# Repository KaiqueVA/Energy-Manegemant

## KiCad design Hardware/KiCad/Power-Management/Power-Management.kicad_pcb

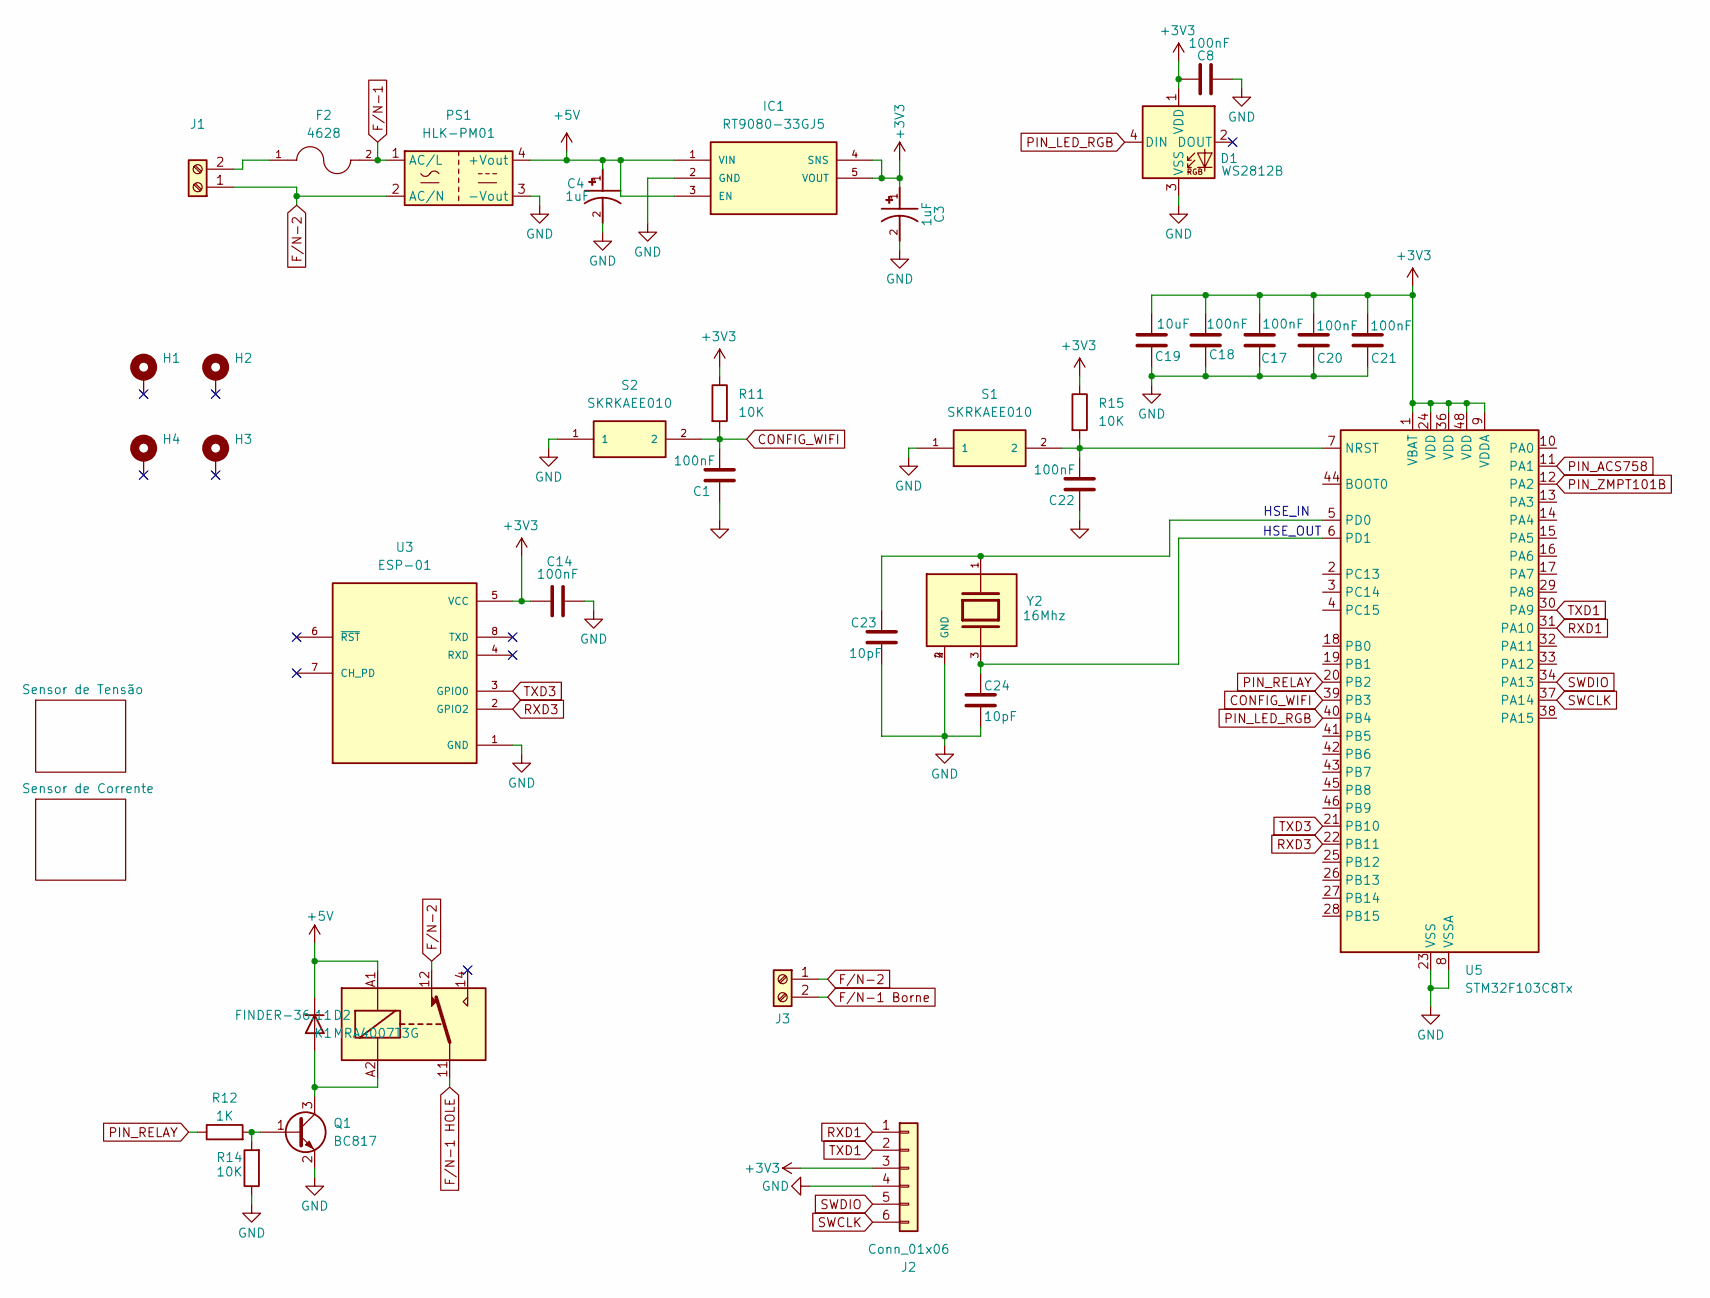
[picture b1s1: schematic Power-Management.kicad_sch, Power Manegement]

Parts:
C1, C8, C14, C17, C18, C20, C21, C22: 100nF; C_0805_2012Metric
C3, C4: 1uF; CAPMP3216X180N; PARTREV N/A
C19: 10uF; C_0805_2012Metric
C23, C24: 10pF; C_0805_2012Metric
D1: WS2812B; LED_WS2812B_PLCC4_5.0x5.0mm_P3.2mm
D2: MRA4007T3G; D_SMA_Handsoldering
F2: 4628; FUSE_4628
H1, H2, H3, H4: MountingHole_Pad; MountingHole_3.2mm_M3_Pad_Via
IC1: RT9080-33GJ5; SOT94P280X100-5N; Mouser_Part_Number 835-RT9080-33GJ5
J1, J3: Screw_Terminal_01x02; TerminalBlock_Altech_AK300-2_P5.00mm
J2: Conn_01x06; Molex_KK-254_AE-6410-06A_1x06_P2.54mm_Vertical
K1: FINDER-36.11; Relay_SPDT_Finder_36.11
PS1: HLK-PM01; Converter_ACDC_Hi-Link_HLK-PMxx
Q1: BC817; SOT-23
R11, R14, R15: 10K; R_0805_2012Metric_Pad1.20x1.40mm_HandSolder
R12: 1K; R_0805_2012Metric_Pad1.20x1.40mm_HandSolder
S1, S2: SKRKAEE010; SKRK; Manufacturer_Part_Number SKRKAEE010
U3: ESP-01; MODULE_ESP-01; PARTREV 1.0
U5: STM32F103C8Tx; LQFP-48_7x7mm_P0.5mm
Y2: 16Mhz; XTAL_TSX-3225_25.0000MF10Z-W; PARTREV N/A

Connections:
+3V3: C3.1, C8.2, C14.1, C17.2, C18.2, C19.2, C20.2, C21.2, D1.1 (VDD), IC1.4 (SNS), IC1.5 (VOUT), J2.3, R11.1, R15.1, U3.5 (VCC), U5.1 (VBAT), U5.9 (VDDA), U5.24 (VDD), U5.36 (VDD), U5.48 (VDD); also elsewhere on the board
+5V: C4.1, D2.1 (K), IC1.1 (VIN), IC1.3 (EN), K1.A1, PS1.4 (+Vout); also elsewhere on the board
CONFIG_WIFI: C1.2, R11.2, S2.2, U5.39 (PB3)
F/N-1: F2.2, PS1.1 (AC/L); also elsewhere on the board
F/N-1 Borne: J3.2; also elsewhere on the board
F/N-1 HOLE: K1.11; also elsewhere on the board
F/N-2: J1.1, J3.1, K1.12, PS1.2 (AC/N); also elsewhere on the board
GND: C1.1, C3.2, C4.2, C8.1, C14.2, C17.1, C18.1, C19.1, C20.1, C21.1, C22.1, C23.1, C24.1, D1.3 (VSS), IC1.2 (GND), J2.4, PS1.3 (-Vout), Q1.2 (E), R14.1, S1.1, S2.1, U3.1 (GND), U5.8 (VSSA), U5.23 (VSS), U5.35 (VSS), U5.47 (VSS), Y2.2 (GND), Y2.4 (GND); also elsewhere on the board
unnamed: D2.2 (A), K1.A2, Q1.3 (C)
unnamed: F2.1, J1.2
unnamed: Q1.1 (B), R12.2, R14.2
unnamed: C22.2, R15.2, S1.2, U5.7 (NRST)
unnamed: C23.2, U5.5 (PD0), Y2.1
unnamed: C24.2, U5.6 (PD1), Y2.3
PIN_ACS758: U5.11 (PA1); also elsewhere on the board
PIN_LED_RGB: D1.4 (DIN), U5.40 (PB4)
PIN_RELAY: R12.1, U5.20 (PB2)
PIN_ZMPT101B: U5.12 (PA2); also elsewhere on the board
RXD1: J2.1, U5.31 (PA10)
RXD3: U3.2 (GPIO2), U5.22 (PB11)
SWCLK: J2.6, U5.37 (PA14)
SWDIO: J2.5, U5.34 (PA13)
TXD1: J2.2, U5.30 (PA9)
TXD3: U3.3 (GPIO0), U5.21 (PB10)

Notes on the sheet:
HSE_IN
HSE_OUT

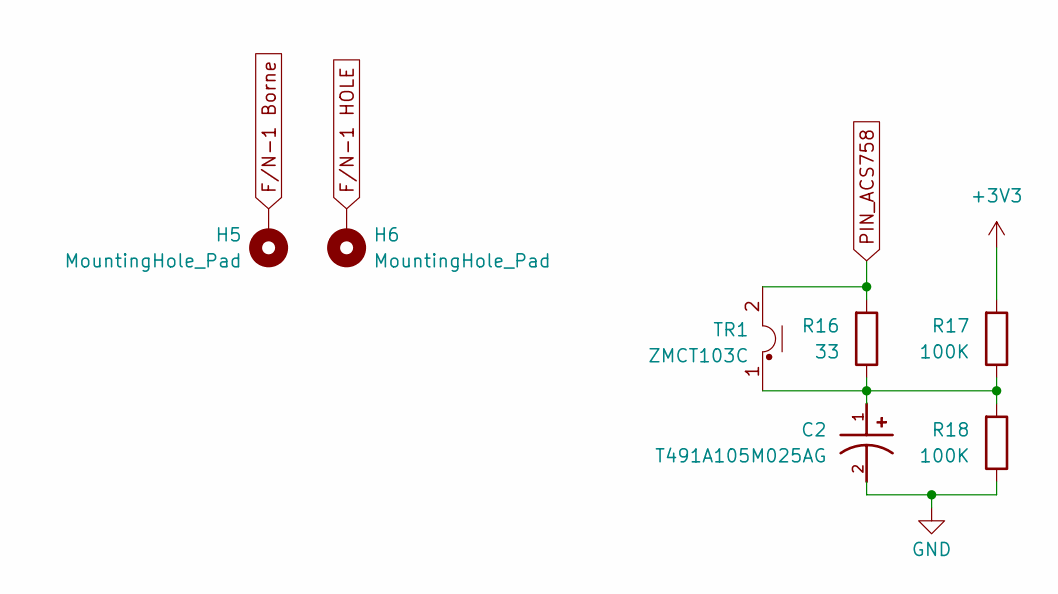
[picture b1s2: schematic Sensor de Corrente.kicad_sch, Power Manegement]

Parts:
C2: T491A105M025AG; CAPMP3216X180N; PARTREV N/A
H5, H6: MountingHole_Pad; MountingHole_2.2mm_M2_Pad_Via
R16: 33; R_0805_2012Metric_Pad1.20x1.40mm_HandSolder
R17, R18: 100K; R_0805_2012Metric_Pad1.20x1.40mm_HandSolder
TR1: ZMCT103C; Transformer_Zeming_ZMCT103C

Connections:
+3V3: R17.2; also elsewhere on the board
F/N-1 Borne: H5.1; also elsewhere on the board
F/N-1 HOLE: H6.1; also elsewhere on the board
GND: C2.2, R18.1; also elsewhere on the board
unnamed: C2.1, R16.1, R17.1, R18.2, TR1.1
PIN_ACS758: R16.2, TR1.2; also elsewhere on the board

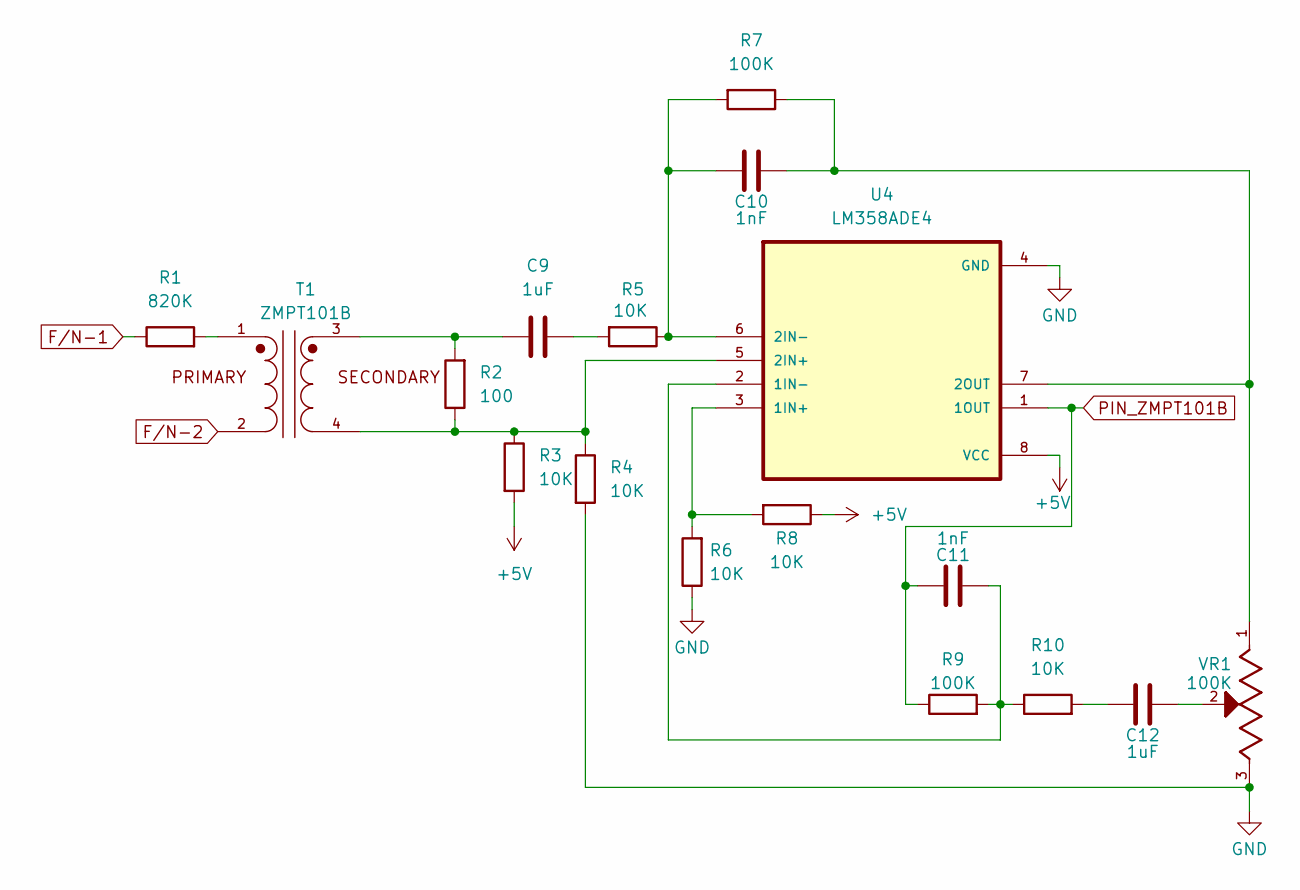
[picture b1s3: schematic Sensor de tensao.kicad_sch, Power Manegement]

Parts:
C9, C12: 1uF; C_0805_2012Metric_Pad1.18x1.45mm_HandSolder
C10, C11: 1nF; C_0805_2012Metric_Pad1.18x1.45mm_HandSolder
R1: 820K; R_0805_2012Metric_Pad1.20x1.40mm_HandSolder
R2: 100; R_0805_2012Metric_Pad1.20x1.40mm_HandSolder
R3, R4, R5, R6, R8, R10: 10K; R_0805_2012Metric_Pad1.20x1.40mm_HandSolder
R7, R9: 100K; R_0805_2012Metric_Pad1.20x1.40mm_HandSolder
T1: ZMPT101B; XFMR_ZMPT101B; PARTREV NA
U4: LM358ADE4; SOIC127P599X175-8N
VR1: 100K; TRIM_3296W-OT1-103LF; PARTREV 05/16

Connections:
+5V: R3.2, R8.1, U4.8 (VCC); also elsewhere on the board
F/N-1: R1.1; also elsewhere on the board
F/N-2: T1.2; also elsewhere on the board
GND: R4.2, R6.1, U4.4 (GND), VR1.3; also elsewhere on the board
unnamed: C9.1, R2.2, T1.3
unnamed: C9.2, R5.2
unnamed: C12.1, R10.2
unnamed: C12.2, VR1.2
unnamed: R1.2, T1.1
unnamed: R6.2, R8.2, U4.3 (1IN+)
unnamed: C11.1, R9.2, R10.1, U4.2 (1IN-)
unnamed: R2.1, R3.1, R4.1, T1.4, U4.5 (2IN+)
unnamed: C10.1, R5.1, R7.2, U4.6 (2IN-)
unnamed: C10.2, R7.1, U4.7 (2OUT), VR1.1
PIN_ZMPT101B: C11.2, R9.1, U4.1 (1OUT); also elsewhere on the board

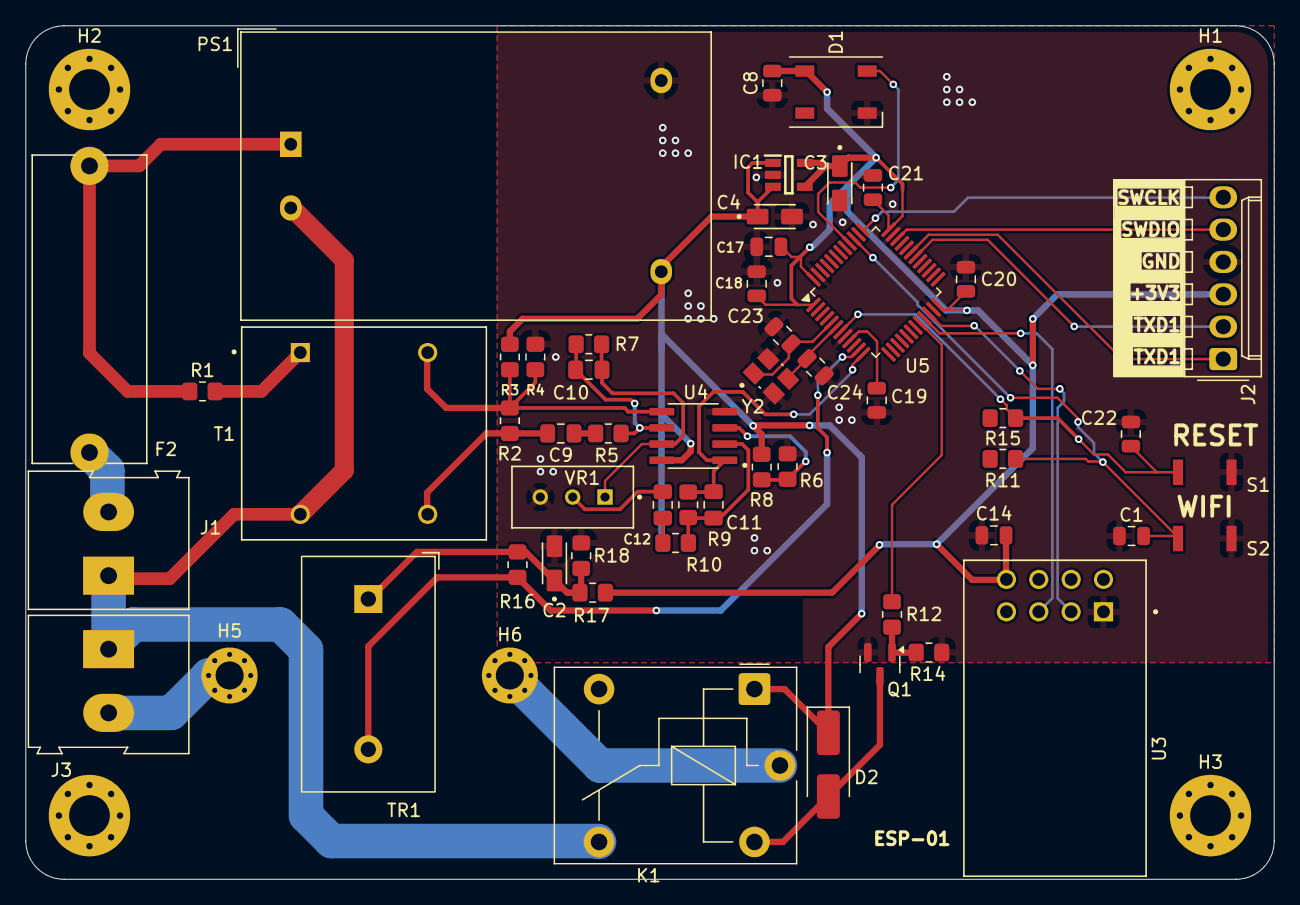
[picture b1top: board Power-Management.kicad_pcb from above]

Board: 2 copper layers, 98.0 x 67.0 mm, 60 parts (0 on the bottom side), 35 nets.

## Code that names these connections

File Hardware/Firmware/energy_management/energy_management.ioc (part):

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Mcu.Name=STM32F103C(8-B)Tx
Mcu.Package=LQFP48
Mcu.UserName=STM32F103C8Tx
PA0-WKUP.Signal=ADCx_IN0
PA1.Signal=ADCx_IN1
PA10.Mode=Asynchronous
PA10.Signal=USART1_RX
PA13.Mode=Serial_Wire
PA13.Signal=SYS_JTMS-SWDIO
PA14.Mode=Serial_Wire
PA14.Signal=SYS_JTCK-SWCLK
PA9.Mode=Asynchronous
PA9.Signal=USART1_TX
PB10.Mode=Asynchronous
PB10.Signal=USART3_TX
PB11.Mode=Asynchronous
PB11.Signal=USART3_RX
PB3.GPIOParameters=GPIO_Label
PB3.GPIO_Label=RELE
PB3.Signal=GPIO_Output
PD0-OSC_IN.Mode=HSE-External-Oscillator
PD0-OSC_IN.Signal=RCC_OSC_IN
PD1-OSC_OUT.Mode=HSE-External-Oscillator
PD1-OSC_OUT.Signal=RCC_OSC_OUT
RCC.SYSCLKFreq_VALUE=40000000
RCC.SYSCLKSource=RCC_SYSCLKSOURCE_PLLCLK
board=custom

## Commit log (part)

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2025-01-11 inital commit
2025-01-11 feat: gitignore
2025-01-12 feat: add dependencies
2025-01-13 fix: resolve env variables not loading issue
2025-01-14 feat: hardware prototype
2025-01-14 feat: project libraries
2025-01-14 project libraries
2025-01-14 feat: project libraries kicad
2025-01-15 feat: hierarchical sheet
2025-01-27 feat: create User entity
2025-01-27 feat: create UserRepository interface
2025-02-01 feat: create TokenService component
2025-02-05 feat: implement JWT token generation and validation service
2025-02-05 feat: token secret env variable
2025-02-22 refactor: exchange of STMF401 for F103
2025-02-22 feat: footprint and step
2025-02-22 feat: text and icons in silkscreen
2025-02-22 refactor: debug-uart silkscreen
2025-03-06 troca de sensor de corrente
2025-03-09 refactor: Voltage transformer Op Amp circuit and current transformer circuit.
2025-03-17 Frontend/Feat: Tela de login
2025-03-24 Revert "feat: create SecurityFilter component"
    This reverts commit 1de7ac62c53f355f53752247d6843d9402539de6.
2025-03-24 feat: create SecurityFilter component
2025-03-26 update: improve UI design in login page
2025-04-06 feat: create CustomUserDetailsService component
2025-04-06 feat: create SecurityConfig component
2025-04-19 feat: firmware initial
2025-04-19 feat: implementation of functions to control hardware through hw_adc_reader
2025-04-19 feat: implementation of functions to process and calculate energy data
2025-04-19 feat: state machine test
2025-04-19 feat: initial commit from log_debug
2025-04-19 feat: implementation of functions to control hardware through
2025-04-19 feat: add log_debug files with formatted printing functions
2025-04-19 feat: Including a LOG after the data is ready to be processed
2025-04-20 feat: Initial Commit from UART Communication
2025-04-23 Feat: Página Dashboard
2025-04-23 Feat: Dashboard page
2025-04-24 Feat: Gráficos do dashboard
2025-04-24 Feat: Tabela de histórico
2025-04-26 feat: add gitignore
2025-05-03 feat: create Auth and User Controllers
2025-05-03 feat: create request and response DTOs
2025-05-03 fix: error key in AuthController
2025-05-04 fix: error id type
2025-05-04 feat: new entity Measurement
2025-05-04 feat: add energy data processing module
2025-05-04 feat: implement communication module with support for AT commands
2025-05-04 feat: add hardware communication module with UART transmit and receive functions
2025-05-04 Enhance DMA and Timer Configuration in energy_management.ioc
    - Updated USART1 RX DMA priority from LOW to VERY HIGH for improved data handling.
    - Changed USART1 TX DMA mode from NORMAL to CIRCULAR to allow continuous data transmission.
    - Added TIM4 configuration with a prescaler of 4000-1 and a period of 10000-1 for timer functionality.
    - Updated MCU pin configuration to include TIM4 and adjusted the total pin count.
    - Registered TIM4 and USART1 interrupts in the NVIC for better interrupt handling.
    - Updated function list to include TIM4 initialization in the project manager settings.
2025-05-04 feat: add support for processing and sending data in the main function
2025-05-04 feat: add UART ESP simulator with commands and data processing
2025-05-05 feat: add DTO for measurement data
2025-05-05 feat: add MeasurementMapper using MapStruct
2025-05-05 feat: add MeasurementRepository interface for DB operations
2025-05-05 feat: implement MeasurementMapper with MapStruct and inject in service
2025-05-05 feat: add MeasurementController with CRUD endpoints
2025-05-05 fix: column names
2025-05-05 fix: column names DTO
2025-05-06 feat: update Measurement entity to use sequence generation and add user relationship
2025-05-06 fix: change delete endpoint to accept Integer id instead of UUID
2025-05-06 feat: link measurements to user by user_id and use Integer id
2025-05-06 feat: add UUID to Integer mapping methods in MeasurementMapper
2025-05-06 feat: change MeasurementRepository to use Integer as ID and add user_id query method
2025-05-06 feat: associate measurements with users and add user query
2025-05-06 feat: change UserRepository to use UUID as ID type
2025-05-06 refactor: use String for UUID mapping instead of unsafe Integer conversion
2025-05-06 refactor: reorganizar a função HAL_UART_RxCpltCallback para melhorar a legibilidade
2025-05-06 feat: Increased UART DMA buffer and added AT command for Relay
2025-05-06 feat: add wait function for OK response and implement relay control in ESP simulator
2025-05-06 refactor: reorganize HW_COMMS functions and remove unused delay function
2025-05-06 refactor: remove unused AT_INIT case and add timeout handling in COMMS_Process
2025-05-09 Feat: Line chart no dashboard
2025-05-10 fix: Java Linguist
2025-05-11 Add MIT License
2025-05-11 fix: update copyright year and name in LICENSE file
2025-05-23 feat: add HW_COMMS_StopTimeout function to manage timeout state
2025-05-23 feat: add flag_send management and timeout handling in COMMS_Process
2025-05-23 feat: atualizar endpoints de login e envio, e ajustar lógica de comandos no simulador ESP
2025-05-23 Feat: Registro de usuário
2025-05-24 feat: adicionar captura do tempo de tick no loop principal
2025-05-25 feat: ajustar coeficientes do filtro IIR e corrigir tipo de dados no separador de buffer ADC
2025-05-25 feat: renomear funções de filtro IIR para iir_to_ampere e iir_to_voltage, e atualizar chamadas no separador de buffer ADC
2025-05-25 feat: atualizar valor de calibração de energia para melhorar precisão
2025-05-25 fix: remover loop vazio no separador de buffer ADC
2025-05-28 Implementado testes no WiFi
2025-05-29 Feat: Login e logout de usuário
2025-05-30 Feat: Consumo de dados pela API
2025-05-31 feat: adicionar suporte para USART3 e DMA correspondente
2025-05-31 feat: atualizar suporte para USART3 nas funções de comunicação
2025-05-31 fix: corrigir referência do UART para huart1 no log de depuração
2025-05-31 feat: adicionar suporte para USART3 e ajustar configurações de DMA
2025-06-01 fix: adicionar controle de estado para comandos AT de relé
2025-06-01 fix: adicionar definições de pinos para o relé
2025-06-01 fix: reorganizar a inicialização do GPIO para o relé
2025-06-01 fix: ajustar a assinatura da função de parsing e restaurar controle de relé
2025-06-01 fix: atualizar configurações de GPIO e ajustar pinos no arquivo de configuração
2025-06-03 Feat: Quadro de visão geral funcional
2025-06-03 Feat: Novas imagens
2025-06-03 fix: ajustar calibração de energia e corrigir cálculo de corrente
2025-06-04 fix: corrigir taxa de transmissão do USART3 para 9600 bps
2025-06-04 Feat: Endpoints de measurements
2025-06-04 Feat: Measurements service
2025-06-04 fix: adicionar suporte a polling de estado do relé e leitura da porta serial
2025-06-04 fix: corrigir configuração do USART3 para taxa de transmissão de 9600 bps
2025-06-05 Feat: Novos endpoints de measurements
2025-06-05 Feat: Novos endpoints (loucura pura)
2025-06-05 Feat: Script para povoar DB
2025-06-05 Fix: Bloco dashboard
2025-06-05 fix: adicionar lógica de repetição para comando AT+RESET na inicialização
2025-06-05 Feat: Adiciona controle de estado do relé
